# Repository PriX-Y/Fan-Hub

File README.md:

# Fan-Hub
**RP2040 PWM Fan Controller for x4 fan**

i made becuse this summer in europa is so hot: 43c but i didt have fan what have enough control for me so i made that, becuse my so bad soldring skill i make this full THT

# Programs
**Kicad - 10.1**

**Autodesk Fusion**

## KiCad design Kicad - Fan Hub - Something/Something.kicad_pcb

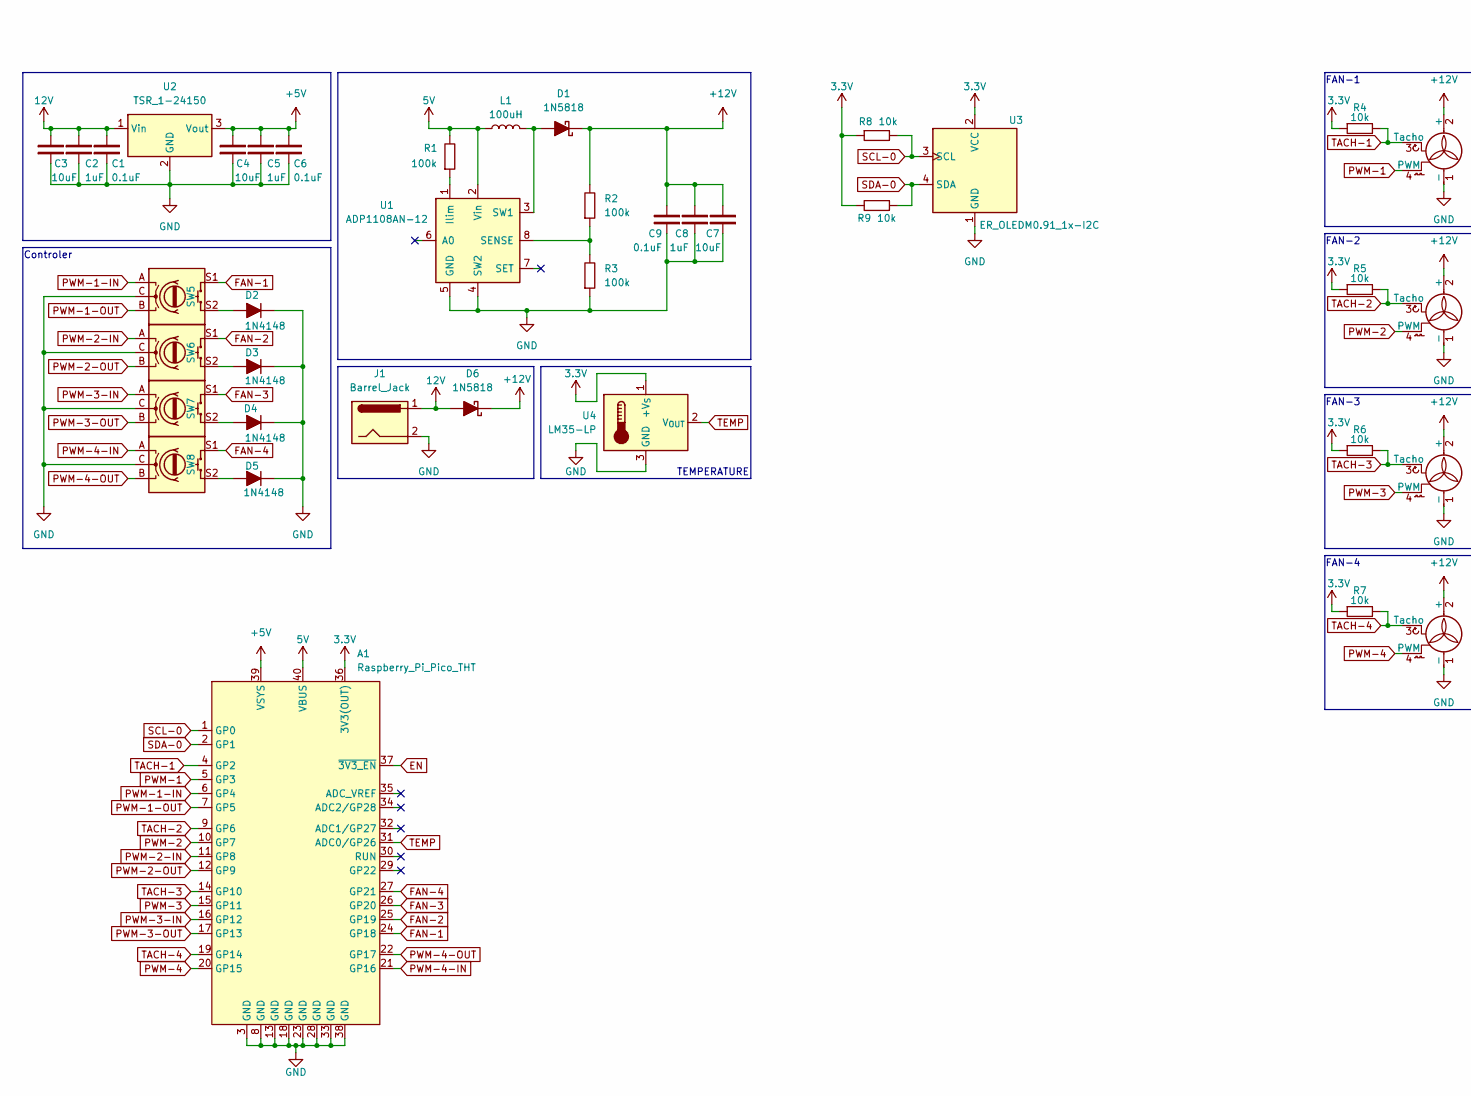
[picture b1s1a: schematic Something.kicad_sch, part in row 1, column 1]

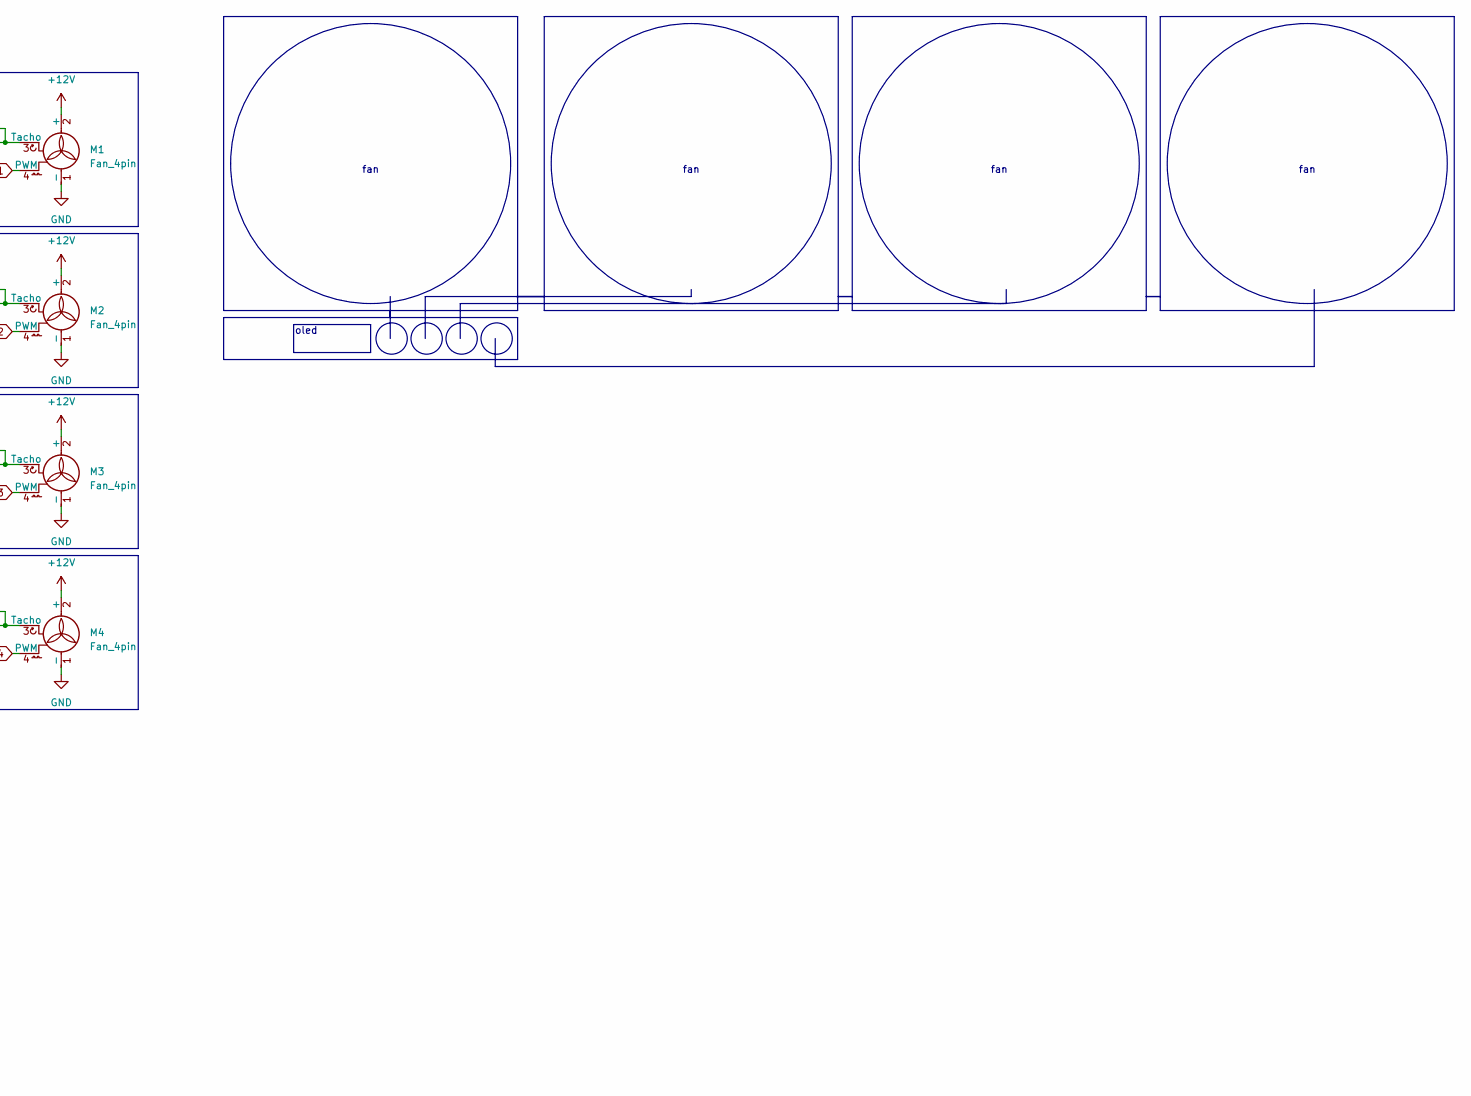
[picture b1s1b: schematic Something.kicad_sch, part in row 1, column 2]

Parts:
A1: Raspberry_Pi_Pico_THT; raspberry_pi_pico_THT
C1, C6, C9: 0.1uF; C_Disc_D5.0mm_W2.5mm_P2.50mm
C2, C5, C8: 1uF; C_Disc_D5.0mm_W2.5mm_P2.50mm
C3, C4, C7: 10uF; C_Disc_D5.0mm_W2.5mm_P2.50mm
D1, D6: 1N5818; D_DO-41_SOD81_P7.62mm_Horizontal
D2, D3, D4, D5: 1N4148; D_DO-35_SOD27_P7.62mm_Horizontal
J1: Barrel_Jack; BarrelJack_SwitchcraftConxall_RAPC10U_Horizontal
L1: 100uH; L_Axial_L5.3mm_D2.2mm_P10.16mm_Horizontal_Vishay_IM-1
M1, M2, M3, M4: Fan_4pin; FanPinHeader_1x04_P2.54mm_Vertical
R1, R2, R3: 100k; R_Axial_DIN0207_L6.3mm_D2.5mm_P10.16mm_Horizontal
R4, R5, R6, R7, R8, R9: 10k; R_Axial_DIN0207_L6.3mm_D2.5mm_P10.16mm_Horizontal
SW5, SW6, SW7, SW8: RotaryEncoder_Switch; RotaryEncoder_Bourns_Horizontal_PEC12R-2x17F-Sxxxx
U1: ADP1108AN-12; DIP-8_W7.62mm
U2: TSR_1-24150; Converter_DCDC_TRACO_TSR-1_THT
U3: ER_OLEDM0.91_1x-I2C
U4: LM35-LP; TO-92_Inline

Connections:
3.3V: A1.36 (3V3(OUT)), R4.1, R5.1, R6.1, R7.1, R8.1, R9.2, U3.2 (VCC), U4.1 (+V_{S})
5V: A1.40 (VBUS), L1.1, R1.2, U1.2 (Vin)
12V: C1.2, C2.2, C3.2, D6.2 (A), J1.1, U2.1 (Vin)
+5V: A1.39 (VSYS), C4.2, C5.2, C6.2, U2.3 (Vout)
+12V: C7.2, C8.2, C9.2, D1.1 (K), D6.1 (K), M1.2 (+), M2.2 (+), M3.2 (+), M4.2 (+), R2.2
EN: A1.37 (~3V3_EN)
FAN-1: A1.24 (GP18), SW5.S1
FAN-2: A1.25 (GP19), SW6.S1
FAN-3: A1.26 (GP20), SW7.S1
FAN-4: A1.27 (GP21), SW8.S1
GND: A1.3 (GND), A1.8 (GND), A1.13 (GND), A1.18 (GND), A1.23 (GND), A1.28 (GND), A1.33 (GND), A1.38 (GND), C1.1, C2.1, C3.1, C4.1, C5.1, C6.1, C7.1, C8.1, C9.1, D2.1 (K), D3.1 (K), D4.1 (K), D5.1 (K), J1.2, M1.1 (-), M2.1 (-), M3.1 (-), M4.1 (-), R3.1, SW5.C, SW5.SH, SW6.C, SW7.C, SW8.C, U1.4 (SW2), U1.5 (GND), U2.2 (GND), U3.1 (GND), U4.3 (GND)
unnamed: D1.2 (A), L1.2, U1.3 (SW1)
unnamed: D2.2 (A), SW5.S2
unnamed: D3.2 (A), SW6.S2
unnamed: D4.2 (A), SW7.S2
unnamed: D5.2 (A), SW8.S2
unnamed: R1.1, U1.1 (Ilim)
unnamed: R2.1, R3.2, U1.8 (SENSE)
PWM-1: A1.5 (GP3), M1.4 (PWM)
PWM-1-IN: A1.6 (GP4), SW5.A
PWM-1-OUT: A1.7 (GP5), SW5.B
PWM-2: A1.10 (GP7), M2.4 (PWM)
PWM-2-IN: A1.11 (GP8), SW6.A
PWM-2-OUT: A1.12 (GP9), SW6.B
PWM-3: A1.15 (GP11), M3.4 (PWM)
PWM-3-IN: A1.16 (GP12), SW7.A
PWM-3-OUT: A1.17 (GP13), SW7.B
PWM-4: A1.20 (GP15), M4.4 (PWM)
PWM-4-IN: A1.21 (GP16), SW8.A
PWM-4-OUT: A1.22 (GP17), SW8.B
SCL-0: A1.1 (GP0), R8.2, U3.3 (SCL)
SDA-0: A1.2 (GP1), R9.1, U3.4 (SDA)
TACH-1: A1.4 (GP2), M1.3 (Tacho), R4.2
TACH-2: A1.9 (GP6), M2.3 (Tacho), R5.2
TACH-3: A1.14 (GP10), M3.3 (Tacho), R6.2
TACH-4: A1.19 (GP14), M4.3 (Tacho), R7.2
TEMP: A1.31 (ADC0/GP26), U4.2 (V_{OUT})

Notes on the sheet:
fan
Controler
FAN-4
FAN-3
TEMPERATURE
oled
FAN-1
FAN-2

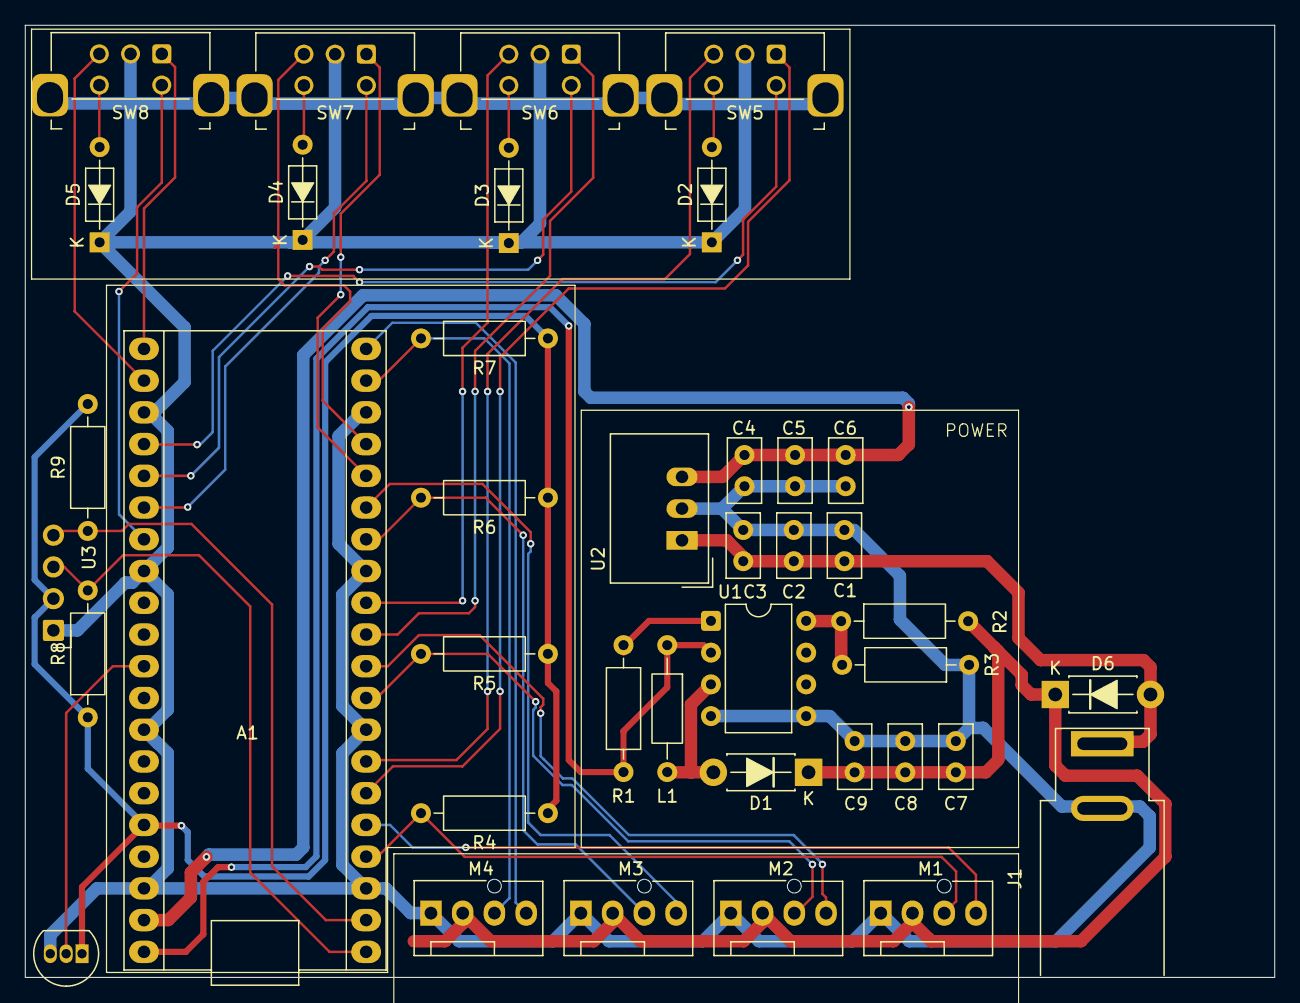
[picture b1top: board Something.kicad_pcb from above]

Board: 2 copper layers, 100.0 x 76.2 mm, 39 parts (0 on the bottom side), 36 nets.
